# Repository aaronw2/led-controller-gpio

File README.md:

Daughter board for Wrover32 LED Controller

This daughter board is designed to augment the Wrover32 LED controller
board by adding additional GPIO I/O support in addition to an
accelerometer and the ability to switch the fan on and off.  Two status
LEDs are also present, one for 3.3V power and the other for when the
fan is enabled.

The I2C termination can be enabled or disabled by SW1.

SW1-1: SCL pull-up enable
SW1-2: SDA pull-up enable
SW1-3: Interrupt pull-up enable

GPIO is controlled by a PCA9575HF and the accelerometer is a MXC4005XC

I2C Addresses:
PCA9575HF: 0x20
BMX160: 0x68
ADS1110A0IDBVR: 1001000 0x48

U1: NXP PCA9575HF,118
U2: Bosch BMX160
U3: Texas Instruments ADS1110A0IDBVR
SW1: Würth Elektronik 416131160803
C1-C7, C9, C14: 1uF X7R 0603 (1608) capacitor
C8,C10,C11,C13,C15: 0.1uF X7R 0603 (1608) capacitor
C12: 10uF X7R 0603 (1608) capacitor
D1: Toshiba CCSA15S30,L3F (protection)
D2: Würth Elektronik Red LED 150060RS75000
D3: Würth Elektronik Green LED 150060GS55040
Q1: Infineon BSS214NW
R1, R3: 4.7K 0603 (1608)
R2: 3.9K 0603 (1608)
RN1: 4.7K, 4x0603 convex, Bourns CAY16-4701F4LF

All components are available from Digikey.

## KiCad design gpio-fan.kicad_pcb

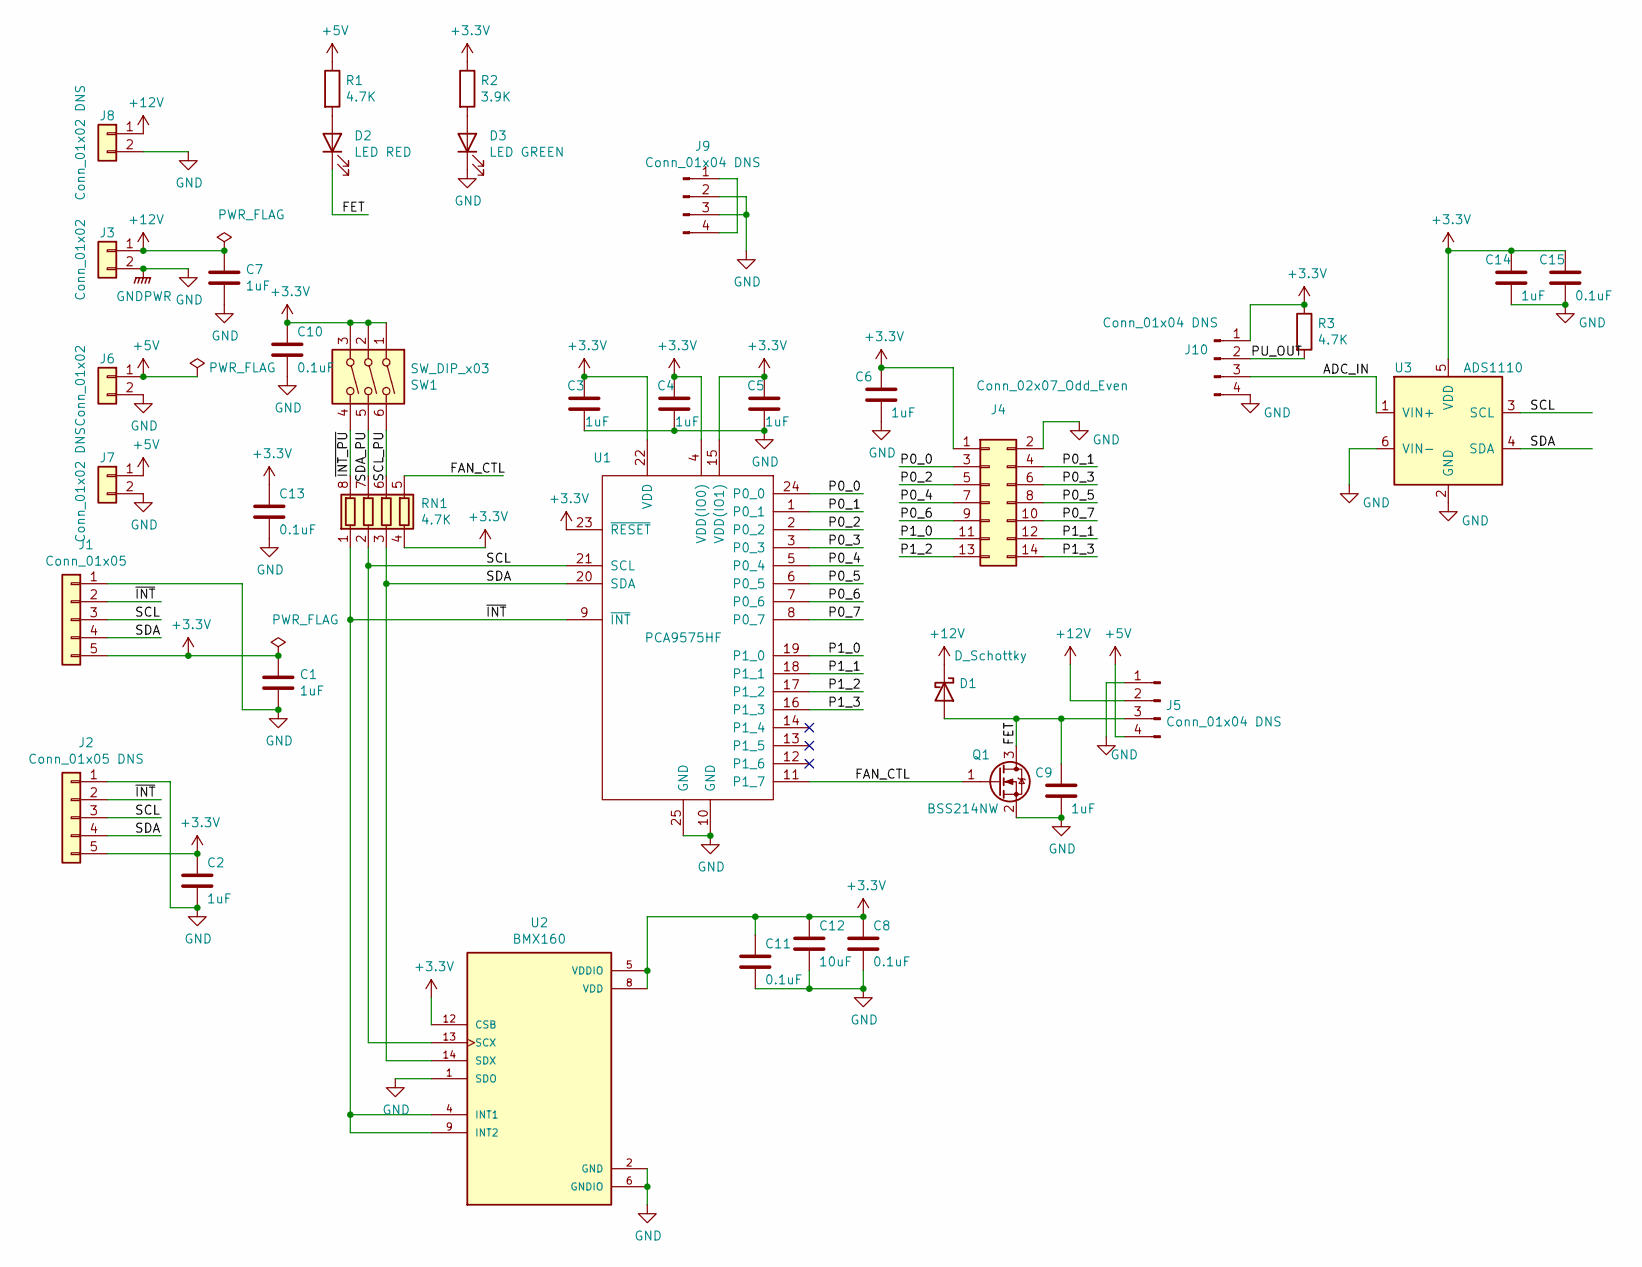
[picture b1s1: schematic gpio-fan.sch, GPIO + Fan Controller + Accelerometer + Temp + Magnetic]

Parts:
C1, C2, C3, C4, C5, C6, C7, C9, C14: 1uF; C_0603_1608Metric; MPN CL10B105KP8NNNC
C8, C10, C11, C13, C15: 0.1uF; C_0603_1608Metric; MPN CL10B104KO8WPNC
C12: 10uF; C_0603_1608Metric; MPN GRT188R61E106ME13D
D1: D_Schottky; D_0603_1608Metric; MPN CCS15S30,L3F
D2: LED RED; LED_0603_1608Metric; MPN 150060RS75000
D3: LED GREEN; LED_0603_1608Metric; MPN 150060GS55040
J1: Conn_01x05; PinSocket_1x05_P1.27mm_Vertical; MPN SLM-105-01-L-S
J2: Conn_01x05 DNS; PinHeader_1x05_P2.54mm_Vertical
J3, J6: Conn_01x02; PinSocket_1x02_P1.27mm_Vertical; MPN SLM-102-01-S-S
J4: Conn_02x07_Odd_Even; PinHeader_2x07_P2.54mm_Horizontal; MPN BHR-14-HUA-ML
J5: Conn_01x04 DNS; PinHeader_1x04_P2.54mm_Vertical; MPN 1719710104
J7: Conn_01x02 DNS; PinHeader_1x02_P1.27mm_Vertical
J8: Conn_01x02 DNS; PinHeader_1x02_P2.54mm_Vertical
J9: Conn_01x04 DNS; PinHeader_1x04_P2.54mm_Vertical
J10: Conn_01x04 DNS; PinHeader_1x04_P1.27mm_Vertical
Q1: BSS214NW; SOT-323_SC-70; MPN BSS214NWH6327XTSA1
R1, R3: 4.7K; R_0603_1608Metric; MPN RC0603FR-071KL
R2: 3.9K; R_0603_1608Metric; MPN CR0603-FX-3901ELF
RN1: 4.7K; R_Array_Convex_4x0603; MPN CAY16-4701F4LF
SW1: SW_DIP_x03; SW_DIP_SPSTx03_Slide_Wurth_416131160803_8.89x4.98mm_W2.65mm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; MPN 416131160803
U1: PCA9575HF; Texas_S-PVQFN-N24_EP2.1x2.1mm; MPN PCA9575HF,118
U2: BMX160; PQFN50P250X300X100-14N; PARTREV 1.2
U3: ADS1110; SOT-23-6; MPN ADS1110A0IDBVR

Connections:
+3V3: C1.1, C2.1, C3.1, C4.1, C5.1, C6.1, C8.1, C10.1, C11.1, C12.1, C13.1, C14.1, C15.1, J1.5, J2.5, J4.1, J10.1, R2.1, R3.1, RN1.4 (R4.1), SW1.1, SW1.2, SW1.3, U1.4 (VDD(IO0)), U1.15 (VDD(IO1)), U1.22 (VDD), U1.23 (~RESET), U2.5 (VDDIO), U2.8 (VDD), U2.12 (CSB), U3.5 (VDD)
+5V: J5.4, J6.1, J7.1, R1.1
+12V: C7.1, D1.1 (K), J3.1, J5.2, J8.1
/ADC_IN: J10.3, U3.1 (VIN+)
/FAN_CTL: Q1.1 (G), RN1.5 (R4.2), U1.11 (P1_7)
/FET: C9.1, D1.2 (A), D2.1 (K), J5.3, Q1.3 (D)
/P0_0: J4.3, U1.24 (P0_0)
/P0_1: J4.4, U1.1 (P0_1)
/P0_2: J4.5, U1.2 (P0_2)
/P0_3: J4.6, U1.3 (P0_3)
/P0_4: J4.7, U1.5 (P0_4)
/P0_5: J4.8, U1.6 (P0_5)
/P0_6: J4.9, U1.7 (P0_6)
/P0_7: J4.10, U1.8 (P0_7)
/P1_0: J4.11, U1.19 (P1_0)
/P1_1: J4.12, U1.18 (P1_1)
/P1_2: J4.13, U1.17 (P1_2)
/P1_3: J4.14, U1.16 (P1_3)
/PU_OUT: J10.2, R3.2
/SCL: J1.3, J2.3, RN1.2 (R2.1), U1.21 (SCL), U2.13 (SCX), U3.3 (SCL)
/SCL_PU: RN1.6 (R3.2), SW1.6
/SDA: J1.4, J2.4, RN1.3 (R3.1), U1.20 (SDA), U2.14 (SDX), U3.4 (SDA)
/SDA_PU: RN1.7 (R2.2), SW1.5
/~INT: J1.2, J2.2, RN1.1 (R1.1), U1.9 (~INT), U2.4 (INT1), U2.9 (INT2)
/~INT_PU: RN1.8 (R1.2), SW1.4
GND: C1.2, C2.2, C3.2, C4.2, C5.2, C6.2, C7.2, C8.2, C9.2, C10.2, C11.2, C12.2, C13.2, C14.2, C15.2, D3.1 (K), J1.1, J2.1, J3.2, J4.2, J5.1, J6.2, J7.2, J8.2, J9.2, J9.3, J10.4, Q1.2 (S), U1.10 (GND), U1.25 (GND), U2.1 (SDO), U2.2 (GND), U2.3 (GND), U2.6 (GNDIO), U2.7 (GND), U3.2 (GND), U3.6 (VIN-)
unnamed: D2.2 (A), R1.2
unnamed: D3.2 (A), R2.2
unnamed: J9.1, J9.4

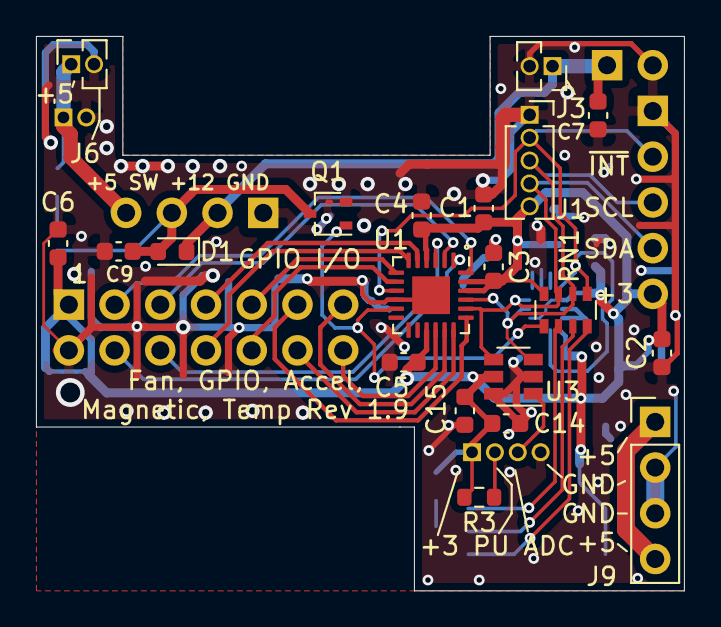
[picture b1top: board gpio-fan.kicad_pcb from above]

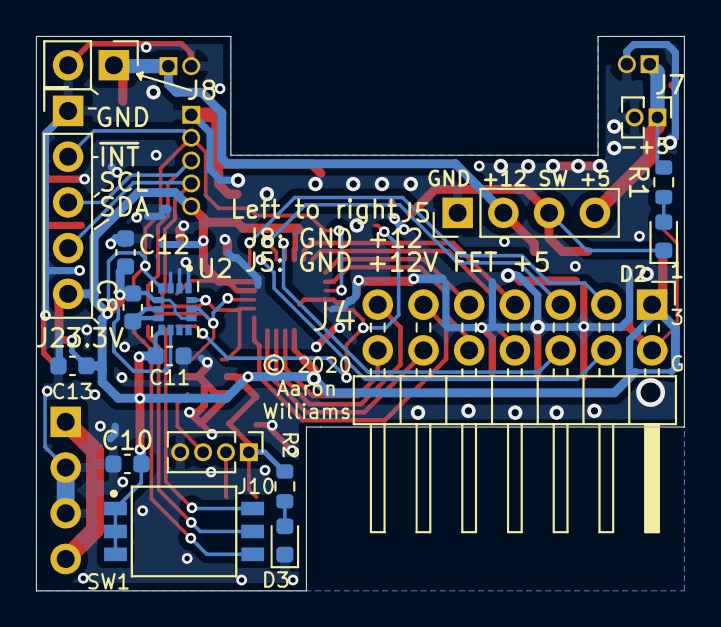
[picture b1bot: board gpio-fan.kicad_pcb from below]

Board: 2 copper layers, 36.0 x 30.8 mm, 37 parts (17 on the bottom side), 29 nets.

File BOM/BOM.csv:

Refs,Value,Footprint,Quantity,DESC,MFR,MPN,SPR,SPN,SPURL
SW1,SW_DIP_x03,Aaron:SW_DIP_SPSTx03_Slide_Wurth_416131160803_8.89x4.98mm_W2.65mm_P1.27mm,1,-,Würth Elektronik,416131160803,Digikey,732-3853-1-ND,https://www.digikey.com/products/en/switches/dip-switches/19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
C8;C11;C13;C15;C10,0.1uF,Capacitor_SMD:C_0603_1608Metric,5,-,Samsung,CL10B104KO8WPNC,Digikey,1276-6582-1-ND,-
C12,10uF,Capacitor_SMD:C_0603_1608Metric,1,-,Murata Electronics,GRT188R61E106ME13D,Digikey,490-12323-1-ND,-
C1;C3;C4;C5;C6;C2;C7;C9;C14,1uF,Capacitor_SMD:C_0603_1608Metric,9,-,Samsung,CL10B105KP8NNNC,Digikey,1276-1946-1-ND,-
J4,Conn_02x07_Odd_Even,Connector_PinHeader_2.54mm:PinHeader_2x07_P2.54mm_Horizontal,1,-,Adam Tech,BHR-14-HUA-ML,Digikey,2057-BHR-14-HUA-ML-ND,https://www.digikey.com/product-detail/en/adam-tech/BHR-14-H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
J3;J6,Conn_01x02,Connector_PinSocket_1.27mm:PinSocket_1x02_P1.27mm_Vertical,2,-,Samtec Inc.,SLM-102-01-S-S,Digikey,SAM9931-ND,https://www.digikey.com/products/en?mpart=SLM-102-01-S-S&v=612
J1,Conn_01x05,Connector_PinSocket_1.27mm:PinSocket_1x05_P1.27mm_Vertical,1,-,Samtec Inc.,SLM-105-01-L-S,Digikey,SAM11788-ND,https://www.digikey.com/product-detail/en/samtec-inc/SLM-105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
D1,D_Schottky,Diode_SMD:D_0603_1608Metric,1,-,Toshiba Semiconductor and Storage,"CCS15S30,L3F",Digikey,CCS15S30L3FCT-ND,https://www.digikey.com/products/en/discrete-semiconductor-p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
D3,LED GREEN,LED_SMD:LED_0603_1608Metric,1,-,Würth Elektronik,150060GS55040,Digikey,732-12014-1-ND,https://www.digikey.com/products/en/optoelectronics/led-indi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
D2,LED RED,LED_SMD:LED_0603_1608Metric,1,-,Würth Elektronik,150060RS75000,Digikey,732-4978-1-ND,https://www.digikey.com/products/en/optoelectronics/led-indi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
U2,BMX160,PQFN50P250X300X100-14N,1,"Accelerometer, Gyroscope, Magnetometer, 9 Axis Sensor I²C, SPI Output",Bosch,BMX160,Digikey,828-1087-1-ND,https://www.digikey.com/en/products/detail/bosch-sensortec/B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
U1,PCA9575HF,Package_DFN_QFN:Texas_S-PVQFN-N24_EP2.1x2.1mm,1,-,NXP USA Inc.,"PCA9575HF,118",Digikey,568-4771-1-ND,https://www.digikey.com/products/en/integrated-circuits-ics/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
U3,ADS1110,Package_TO_SOT_SMD:SOT-23-6,1,IC ADC 16BIT SIGMA-DELTA SOT23-6,Texas Instruments,ADS1110A0IDBVR,Digikey,296-25890-1-ND,https://www.digikey.com/en/products/detail/texas-instruments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
Q1,BSS214NW,Package_TO_SOT_SMD:SOT-323_SC-70,1,-,Infineon Technologies,BSS214NWH6327XTSA1,Digikey,BSS214NWH6327XTSA1CT-ND,https://www.digikey.com/products/en/discrete-semiconductor-p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
R2,3.9K,Resistor_SMD:R_0603_1608Metric,1,"3.9 kOhms ±1% 0.1W, 1/10W Chip Resistor 0603 (1608 Metric) Moisture Resistant Thick Film",Bourns Inc.,CR0603-FX-3901ELF,Digikey,CR0603-FX-3901ELFCT-ND,https://www.digikey.com/en/products/detail/bourns-inc/CR0603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
R3;R1,4.7K,Resistor_SMD:R_0603_1608Metric,2,RES SMD 1K OHM 1% 1/10W 0603,Yageo,RC0603FR-071KL,Digikey,311-1.00KHRCT-ND,https://www.digikey.com/product-detail/en/yageo/RC0603FR-071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
RN1,4.7K,Resistor_SMD:R_Array_Convex_4x0603,1,-,Bourns Inc.,CAY16-4701F4LF,Digikey,CAY16-4701F4LFCT-ND,-

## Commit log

2019-12-27 Initial checkin v1.0
2020-04-21 Added large via to match 3.8, minor changes
2020-04-26 Upgraded to revision 1.3, changed temperature sensor and accelerometer.
    This now uses a combined part that should be a lot easier to solder.
    The new ST part also includes a temperature sensor and it is supported
    by the Arduino library.
2020-07-02 Fixed mislabeled capacitor and other minor changes.
2020-12-29 Fixed J6, dimmed LEDs, and added ADC for light sensor
    This also expands the board size where the switches are so that it can be
    better mounted to the main board via the +5V pins near the speaker connector.
2020-12-30 Made minimum via hole size 0.3mm.
2020-12-30 Made minimum via hole size 0.3mm. Bump to 1.7 due to layout changes.
2020-12-31 Changed accelerometer due to unavailability
    The LSM303AGRTR compass/accelerometer/etc. is out of stock in many places
    so this substitutes a LSM6DSL and a LISMDLTR combination instead.
2021-01-04 Changed sensor to LSM9DS1TR due to availability issues.
2021-01-13 V1.9, changed U2 to Bosch BMX180

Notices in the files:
gpio-fan.kicad_pcb:
© 2020 Aaron Williams
© 2020
